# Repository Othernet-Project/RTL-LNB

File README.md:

RTL-LNB
=======

Discussion and development of LNB that is used in conjunction with an rtl-sdr to downconvert L-band to a frequency more usable by the radio. 

Links
=====

http://goughlui.com/2013/11/10/rtl-sdr-a-tool-for-visualizing-broadcast-satellite-signals/
http://digitalbitrate.com/dtv.php?mux=11470&pid=33&live=65&lang=en

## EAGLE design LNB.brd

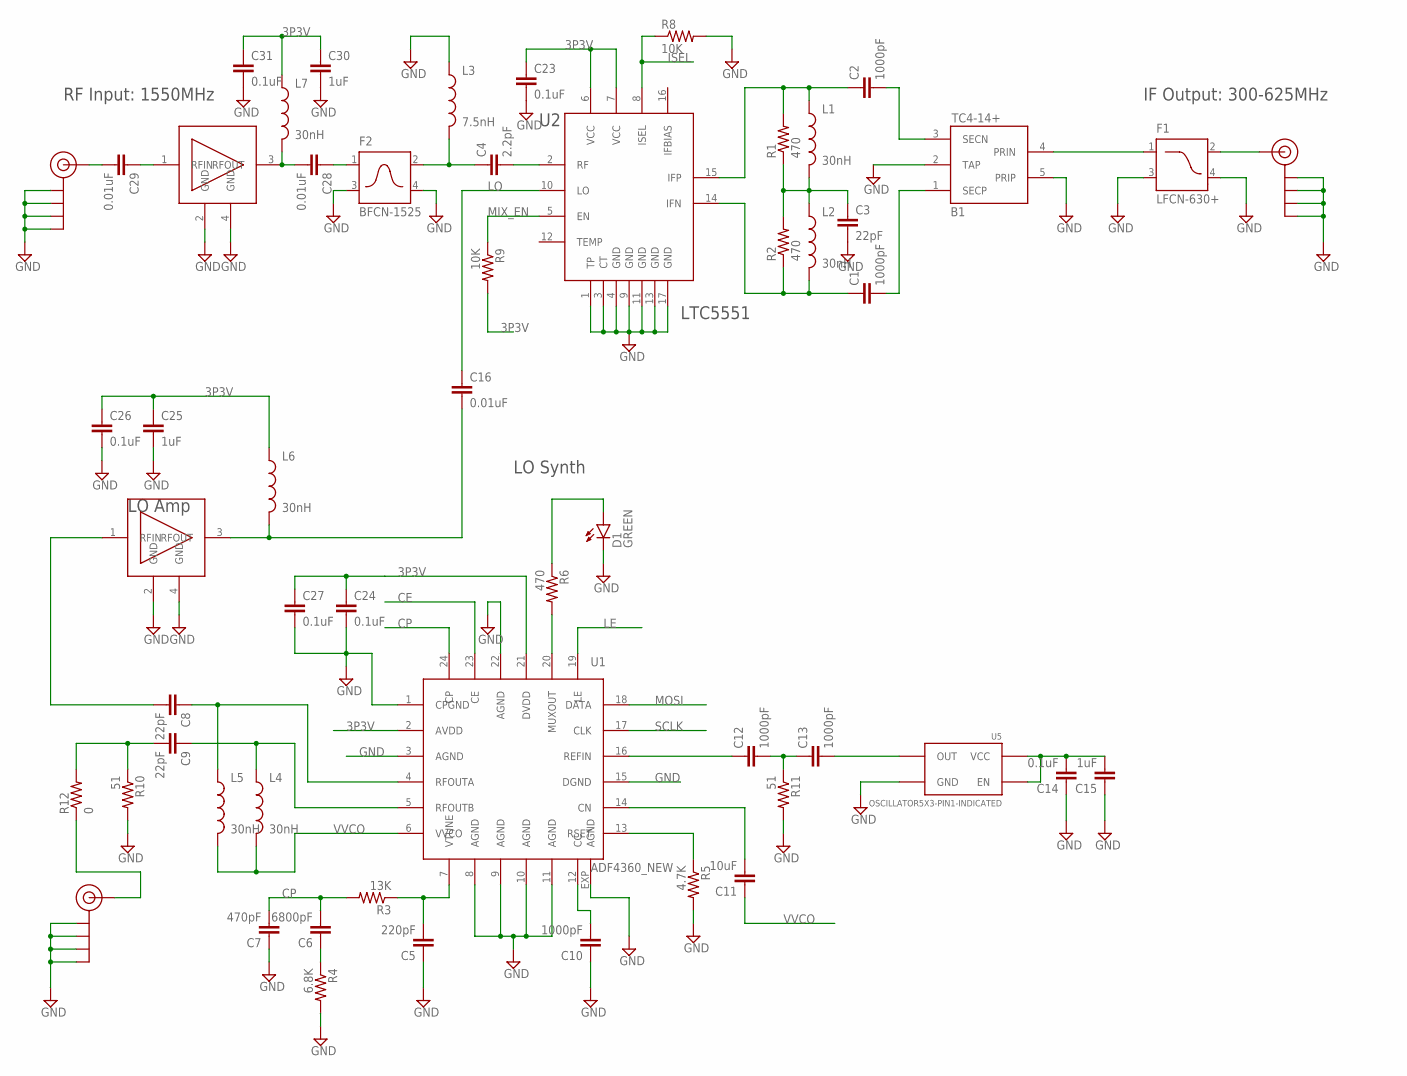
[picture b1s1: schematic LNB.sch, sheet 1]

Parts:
B1: TC4-14+; AT224-1
C1, C2, C10, C12, C13: 1000pF; 0603-CAP
C3, C8, C9: 22pF; 0603-CAP
C4: 2.2pF; 0603-CAP
C5: 220pF; 0603-CAP
C6: 6800pF; 0603-CAP
C7: 470pF; 0603-CAP
C11: 10uF; 0603-CAP
C14, C23, C24, C26, C27, C31: 0.1uF; 0603-CAP
C15: 1uF; 0603-CAP
C16, C28, C29: 0.01uF; 0603-CAP
C25, C30: 1uF; 1206
D1: GREEN; LED-0603
F1: LFCN-630+; FV1206_MC
F2: BFCN-1525; FV1206_MC
J2, J3: SMA_EDGE; SMA-EDGE
J$1: SMA_EDGE; SMA-EDGE
L1, L2, L4, L5, L6, L7: 30nH; 0603
L3: 7.5nH; 0603
R1, R2, R6: 470; 0603-RES
R3: 13K; 0603-RES
R4: 6.8K; 0603-RES
R5: 4.7K; 0603-RES
R8, R9: 10K; 0603-RES
R10, R11: 51; 0603-RES
R12: 0; 0603-RES
U1: ADF4360_NEW; LFCSP24
U2: LTC5551; QFN16-4X4
U5: OSCILLATOR5X3-PIN1-INDICATED; CRYSTAL-OSC-SMD-5X3
U6, U7: PGA-105+; SOT-89

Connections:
3P3V: C14.2, C15.2, C23.1, C24.1, C25.1, C26.1, C27.1, C30.1, C31.1, L6.1, L7.1, R9.2, U1.2 (AVDD), U1.21 (DVDD), U2.6 (VCC), U2.7 (VCC), U5.1 (EN), U5.4 (VCC); also elsewhere on the board
CE: U1.23 (CE); also elsewhere on the board
CP: C6.2, C7.2, R3.2, U1.24 (CP)
GND: B1.2 (TAP), B1.5 (PRIP), C3.2, C5.1, C7.1, C10.1, C14.1, C15.1, C23.2, C24.2, C25.2, C26.2, C27.2, C30.2, C31.2, D1.C, F1.3 (GND), F1.4 (GND), F2.3 (GND), F2.4 (GND), J2.GND@0 (GND), J2.GND@1 (GND), J2.GND@2 (GND), J2.GND@3 (GND), J3.GND@0 (GND), J3.GND@1 (GND), J3.GND@2 (GND), J3.GND@3 (GND), J$1.GND@0 (GND), J$1.GND@1 (GND), J$1.GND@2 (GND), J$1.GND@3 (GND), L3.1, R4.2, R5.2, R8.2, R10.2, R11.2, U1.1 (CPGND), U1.3 (AGND), U1.8 (AGND), U1.9 (AGND), U1.10 (AGND), U1.11 (AGND), U1.15 (DGND), U1.22 (AGND), U1.EXP (AGND), U2.1 (TP), U2.3 (CT), U2.4 (GND), U2.9 (GND), U2.11 (GND), U2.13 (GND), U2.17 (GND), U5.2 (GND), U6.2 (GND), U6.4 (GND), U7.2 (GND), U7.4 (GND); also elsewhere on the board
ISEL: R8.1, U2.8 (ISEL); also elsewhere on the board
LE: U1.19 (LE); also elsewhere on the board
LO: C16.1, U2.10 (LO)
LO_IN: C8.2, U7.1 (RFIN)
MIX_EN: R9.1, U2.5 (EN); also elsewhere on the board
MOSI: U1.18 (DATA); also elsewhere on the board
unnamed: C2.1, L1.1, R1.2, U2.15 (IFP)
unnamed: C1.1, L2.2, R2.1, U2.14 (IFN)
unnamed: C3.1, L1.2, L2.1, R1.1, R2.2
unnamed: B1.1 (SECP), C1.2
unnamed: B1.3 (SECN), C2.2
unnamed: B1.4 (PRIN), F1.1 (IN)
unnamed: F1.2 (OUT), J$1.SIG (SIGNAL)
unnamed: C29.2, J2.SIG (SIGNAL)
unnamed: C4.1, F2.2 (OUT), L3.2
unnamed: C4.2, U2.2 (RF)
unnamed: C5.2, R3.1, U1.7 (VTUNE)
unnamed: C11.2, U1.14 (CN)
unnamed: C6.1, R4.1
unnamed: C8.1, L5.1, U1.4 (RFOUTA)
unnamed: C9.1, L4.1, U1.5 (RFOUTB)
unnamed: C10.2, U1.12 (CC)
unnamed: D1.A, R6.1
unnamed: R5.1, U1.13 (RSET)
unnamed: R6.2, U1.20 (MUXOUT)
unnamed: C9.2, R10.1, R12.2
unnamed: C29.1, U6.1 (RFIN)
unnamed: C12.2, C13.1, R11.1
unnamed: C13.2, U5.3 (OUT)
unnamed: C12.1, U1.16 (REFIN)
unnamed: C16.2, L6.2, U7.3 (RFOUT)
unnamed: J3.SIG (SIGNAL), R12.1
unnamed: C28.2, L7.2, U6.3 (RFOUT)
unnamed: C28.1, F2.1 (IN)
SCLK: U1.17 (CLK); also elsewhere on the board
VVCO: C11.1, L4.2, L5.2, U1.6 (VVCO)

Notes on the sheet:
RF Input: 1550MHz
IF Output: 300-625MHz
LO Synth
LO Amp
LTC5551

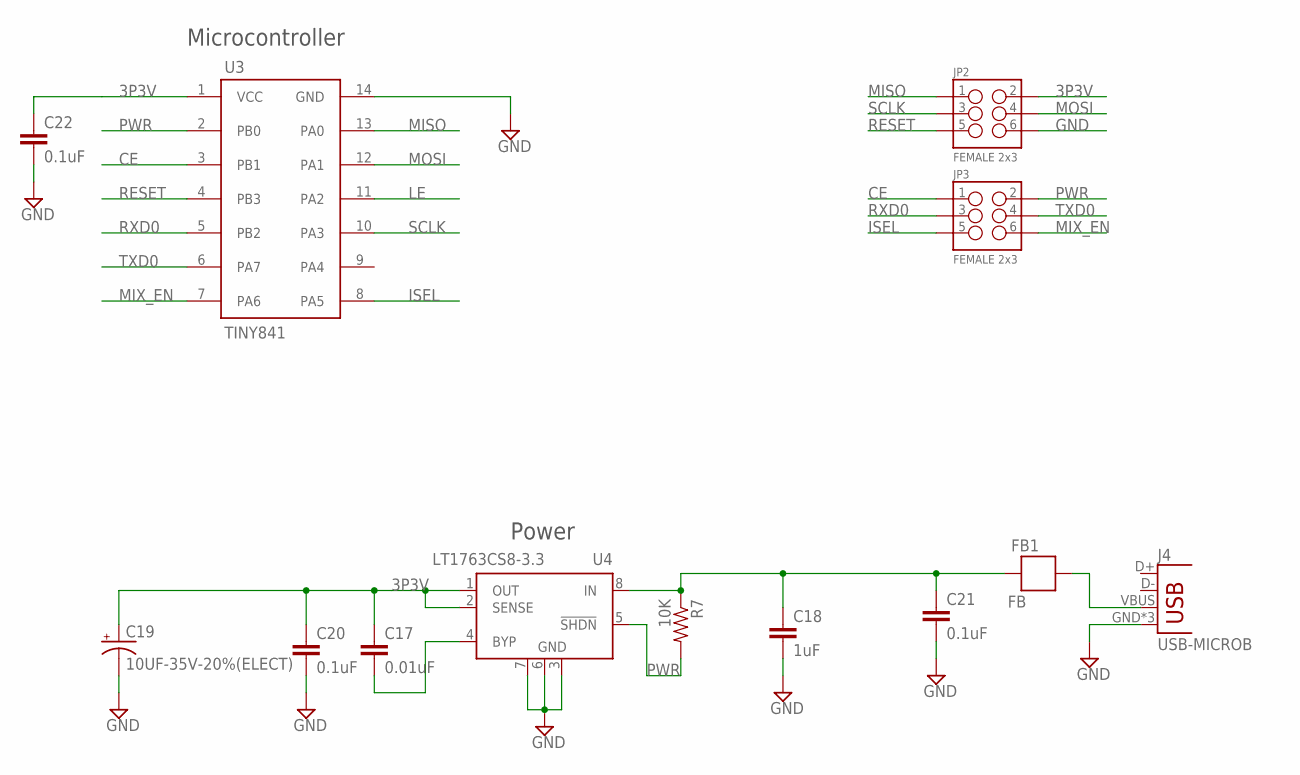
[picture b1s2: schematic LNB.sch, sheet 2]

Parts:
C17: 0.01uF; 0603-CAP
C18: 1uF; 1206
C19: 10UF-35V-20%(ELECT); PANASONIC_C
C20, C21, C22: 0.1uF; 0603-CAP
FB1: FB; 0603
J4: USB-MICROB
JP2, JP3: FEMALE 2x3; 2X3
R7: 10K; 0603-RES
U3: TINY841; SOIC14
U4: LT1763CS8-3.3; SOIC8

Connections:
3P3V: C17.1, C19.+, C20.1, C22.1, JP2.2, U3.1 (VCC), U4.1 (OUT), U4.2 (SENSE); also elsewhere on the board
CE: JP3.1, U3.3 (PB1); also elsewhere on the board
GND: C18.2, C19.-, C20.2, C21.2, C22.2, J4.GND, J4.MT1 (GND), J4.MT2 (GND), JP2.6, U3.14 (GND), U4.3 (GND), U4.6 (GND), U4.7 (GND); also elsewhere on the board
ISEL: JP3.5, U3.8 (PA5); also elsewhere on the board
LE: U3.11 (PA2); also elsewhere on the board
MISO: JP2.1, U3.13 (PA0)
MIX_EN: JP3.6, U3.7 (PA6); also elsewhere on the board
MOSI: JP2.4, U3.12 (PA1); also elsewhere on the board
unnamed: FB1.1, J4.VBUS
unnamed: C18.1, C21.1, FB1.2, R7.1, U4.8 (IN)
unnamed: C17.2, U4.4 (BYP)
PWR: JP3.2, R7.2, U3.2 (PB0), U4.5 (!SHDN)
RESET: JP2.5, U3.4 (PB3)
RXD0: JP3.3, U3.5 (PB2)
SCLK: JP2.3, U3.10 (PA3); also elsewhere on the board
TXD0: JP3.4, U3.6 (PA7)

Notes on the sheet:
Microcontroller
Power

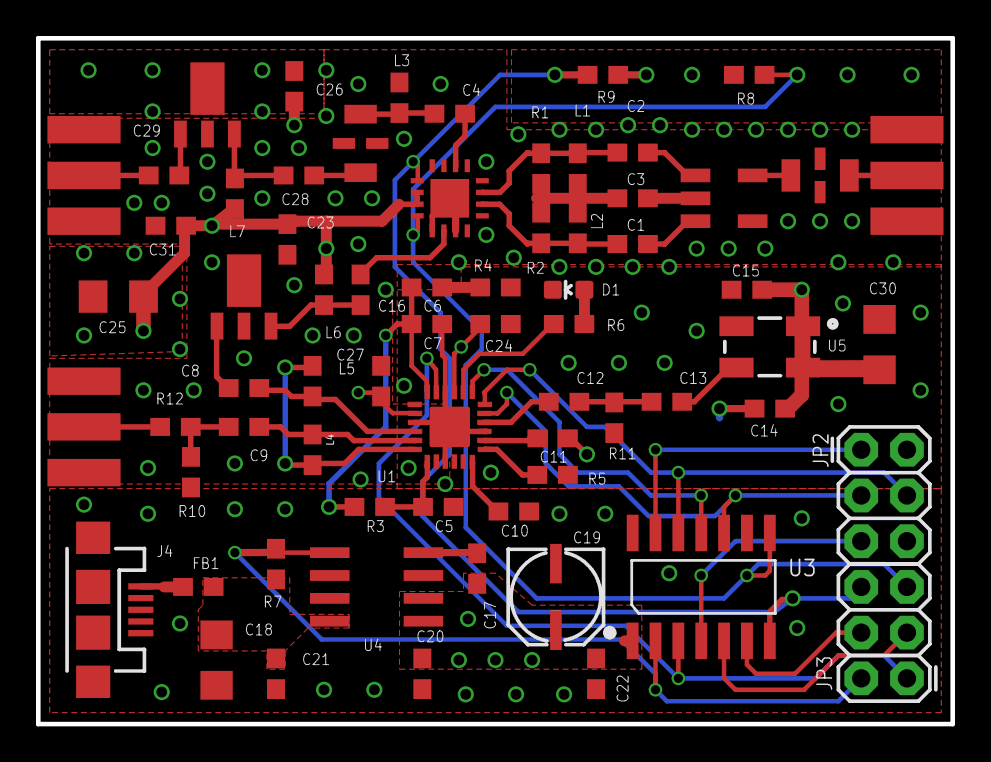
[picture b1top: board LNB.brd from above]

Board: 4 copper layers, 50.8 x 38.1 mm, 68 parts (0 on the bottom side), 48 nets.

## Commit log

2014-10-20 added links to readme
2015-09-05 Update README.md
    changed scope of project from DVB-S reception to hardware LNB.
2015-09-05 Added design files and a picture of the PCB.

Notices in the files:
parts and their libraries:
SparkFun-Passives: Licensing: Creative Commons ShareAlike 4.0 International - https://creativecommons.org/licenses/by-sa/4.0
